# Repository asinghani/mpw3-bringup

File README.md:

# MPW3 Bringup / Characterization

Experiments in bringing up SKY130 MPW-3 chips from the initial tapeout in November 2021. Similarly to [MPW-1](https://github.com/asinghani/mpw1-bringup), the standardized "Caravel" padframe used in this tapeout had hold-time violations between 

## Breakout PCBs

- Characterization PCB [Schematic](boards/mpw3-common/schematic.pdf)
    - Independent voltage regulators for padframe and core (with non-volatile memory)
    - DS1077LU-50 clock generator with 50kHz - 50MHz output frequency + non-volatile memory
    - MCP23017 GPIO expanders for scanning chip I/Os
    - MCP1319 reset supervisor
    - MicroMod-style socket for Caravel chip breakout

- FTDI Breakout [Schematic](boards/uart-breakout/schematic.pdf)
    - Connects characterization PCB to FT232RL for UART access over USB
    - Includes LEDs, switches, and SPI FRAM for use with picoRF0 CPU

- VGA Breakout [Schematic](boards/vga-breakout/schematic.pdf)
    - Breaks out infinite-runner game and pong game to a 2-bit VGA DAC
    - Includes buffer chips for 

## Repo Structure

- `boards/` - KiCAD design files for breakout PCBs
- `parts/` - I/O characterization results for several dies
- `scripts/i2c_iface.py` - Script for interfacing with the voltage regulators, clock generator, and GPIO expanders on the characterization board
- `programs/` - Programs for running on the Caravel processor for the different applications
    - `aes_test.c` - Test the AES core on crypto-accelerator-chip-v2 design
    - `gpio_config_io_dino.py` - GPIO configuration for the VGA runner game
    - `gpio_config_io_pong.py` - GPIO configuration for the VGA pong game
    - `picorf0_test.c` - Test program for the picoRF0 custom CPU core
    - `read_ident.c` - Reads the ROM identifier and build number in the SHA and AES cores
    - `sha256_test.c` - Test the SHA256 core with some test vectors
    - `spi_fram.c` - Test program for using the Caravel SPI master to interface with an FRAM chip
    - `uart_working.c` - Workaround for UART RX on MPW-3 Caravel

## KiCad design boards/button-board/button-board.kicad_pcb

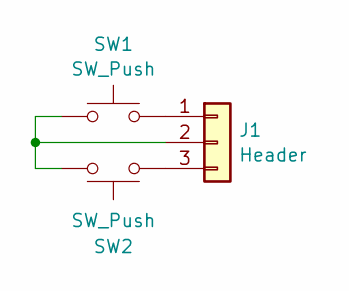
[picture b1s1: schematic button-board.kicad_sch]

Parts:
J1: Header; PinHeader_1x03_P2.54mm_Horizontal
SW1, SW2: SW_Push; SW_Cherry_MX_1.00u_PCB

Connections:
unnamed: J1.1, SW1.2
unnamed: J1.2, SW1.1, SW2.2
unnamed: J1.3, SW2.1

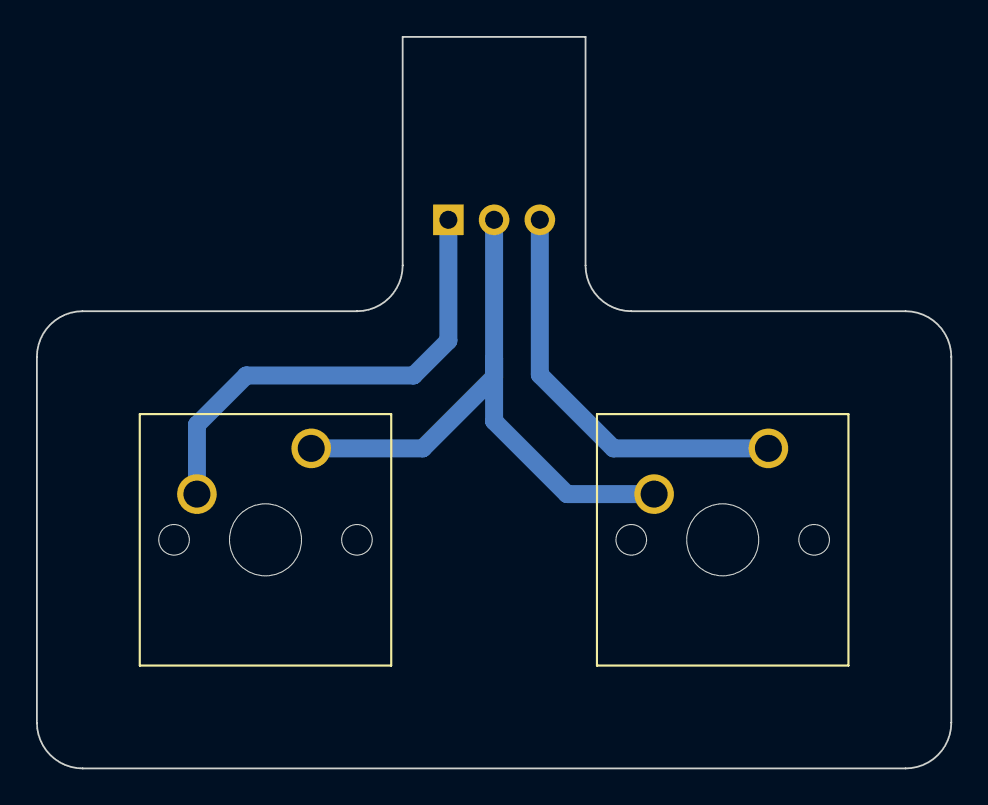
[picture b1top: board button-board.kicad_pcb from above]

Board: 2 copper layers, 50.8 x 40.6 mm, 3 parts (0 on the bottom side), 3 nets.

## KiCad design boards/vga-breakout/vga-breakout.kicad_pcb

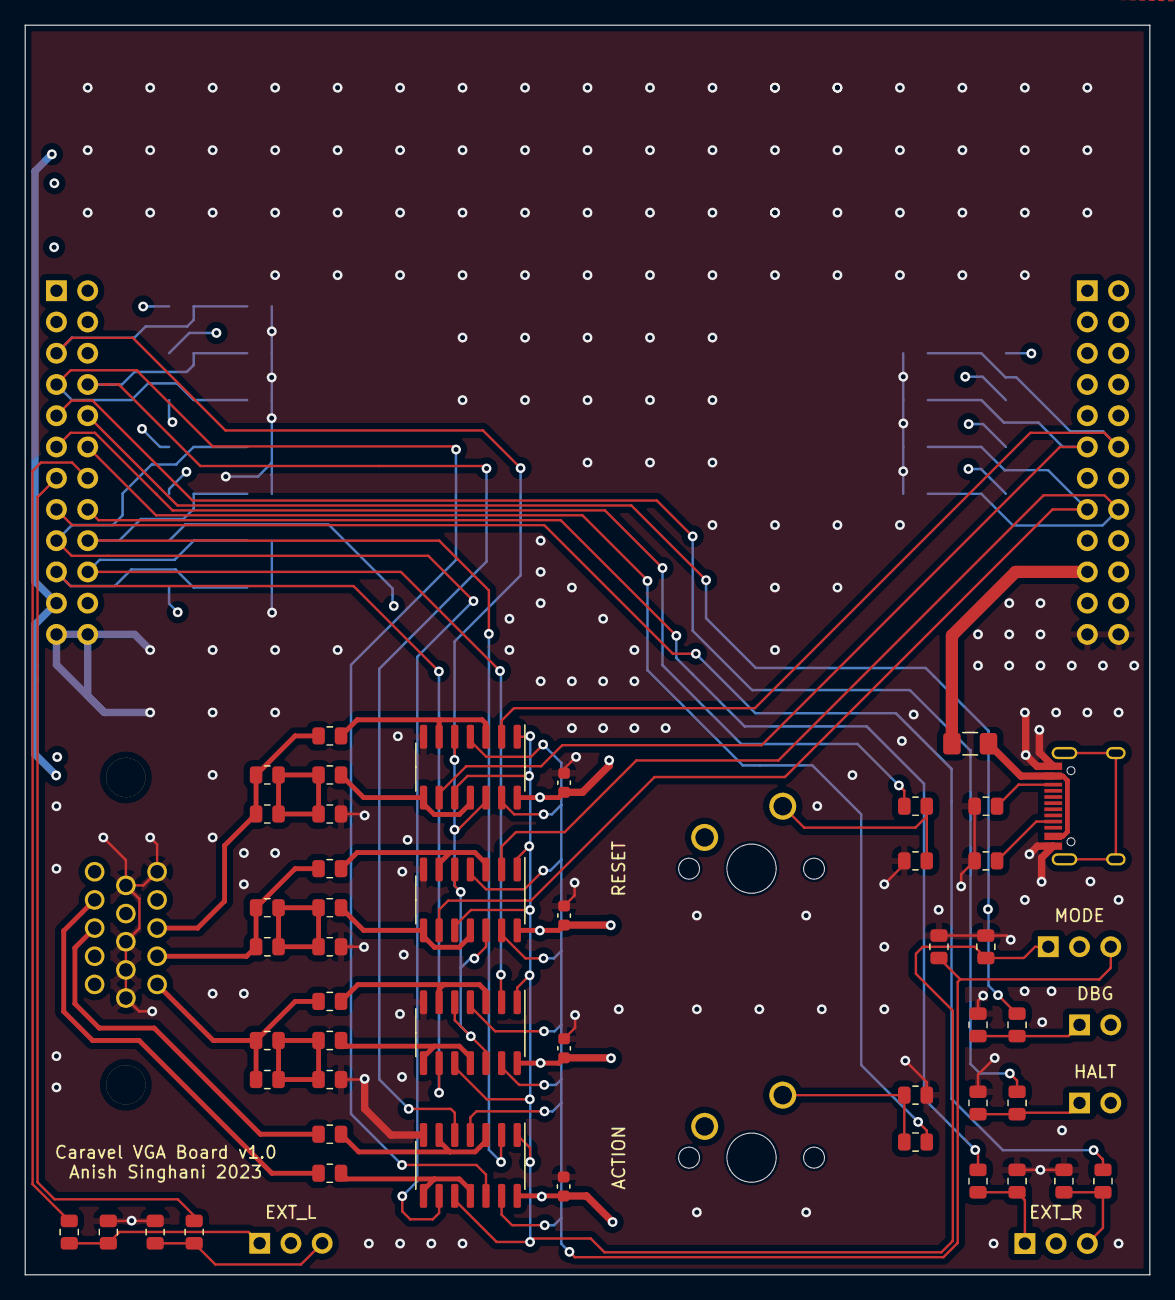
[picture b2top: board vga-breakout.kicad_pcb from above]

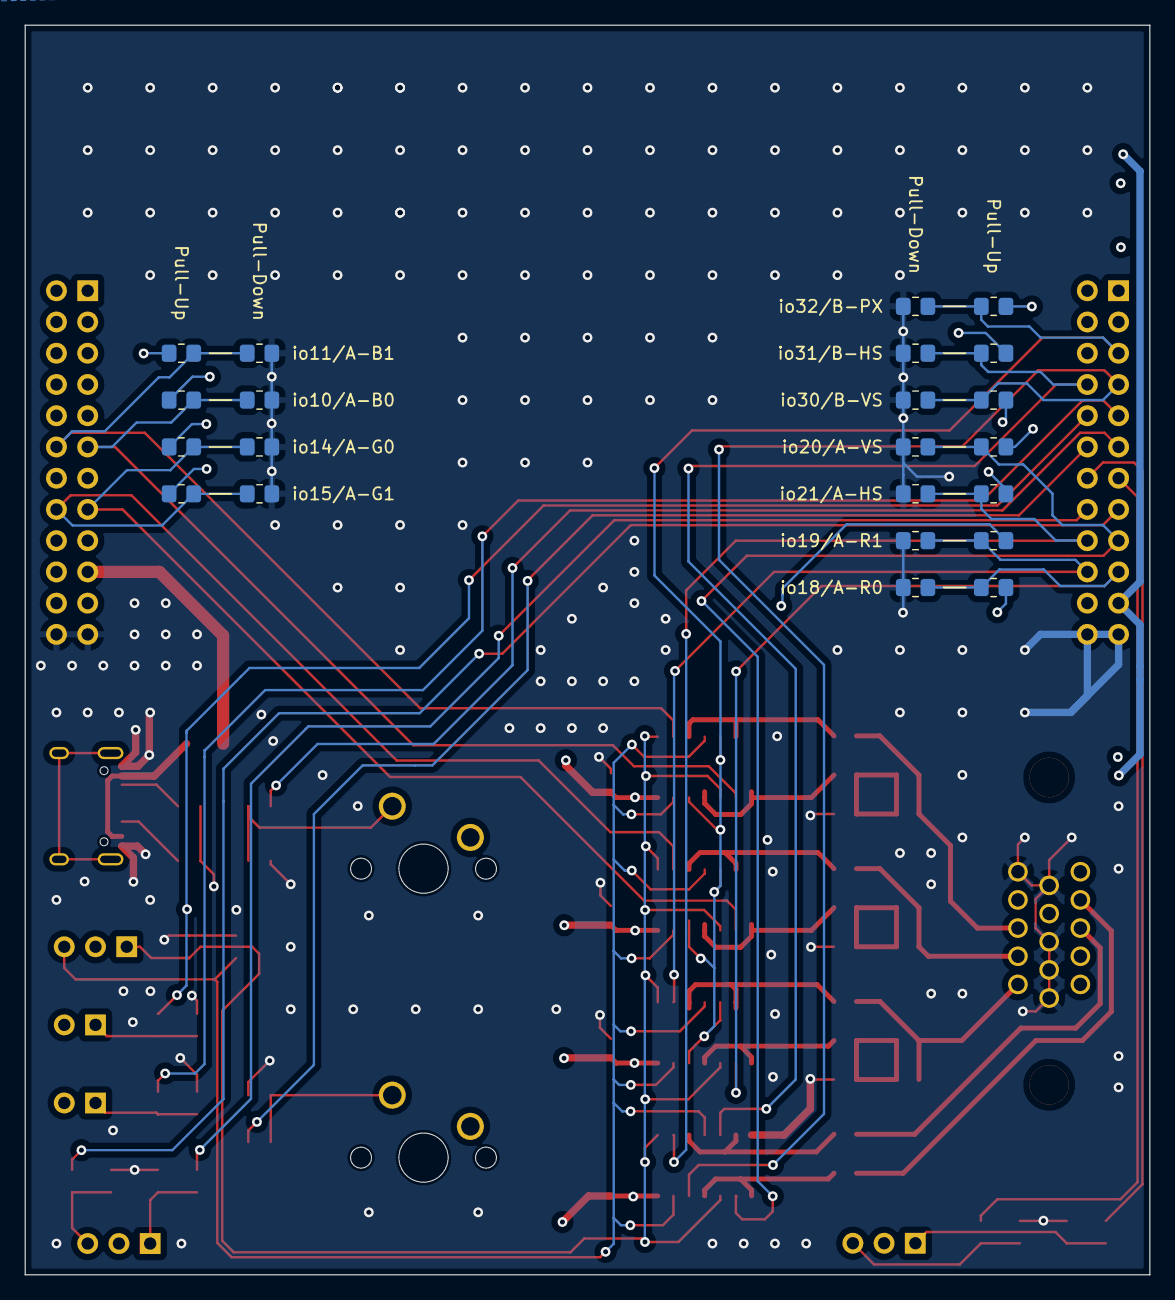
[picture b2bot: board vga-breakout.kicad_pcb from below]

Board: 4 copper layers, 91.4 x 101.6 mm, 79 parts (22 on the bottom side), 51 nets.

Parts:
C2, C3, C4, C5: 1u; C_0603_1608Metric
F1: 500mA; Fuse_1206_3216Metric_Pad1.42x1.75mm_HandSolder
J1: HDR_LEFT; PinHeader_2x12_P2.54mm_Vertical
J2: HDR_RIGHT; PinHeader_2x12_P2.54mm_Vertical
J3: USB_C_Receptacle_USB2.0; USB_C_Receptacle_HRO_TYPE-C-31-M-12
J4: VGA_PLUG; CONN_L77HDE15SD1CH4FVGA_AMP
J5: P1_HDR; PinSocket_1x03_P2.54mm_Vertical
J6: P2_HDR; PinSocket_1x03_P2.54mm_Vertical
JP1: DBG_JMP; PinSocket_1x02_P2.54mm_Vertical
JP2: HALT_JMP; PinSocket_1x02_P2.54mm_Vertical
JP3: MODE_JMP; PinSocket_1x03_P2.54mm_Vertical
R1, R2: 5.1K; R_0805_2012Metric
R3, R4, R5, R6, R11, R12, R13, R14, R66, R67: 10K; R_0805_2012Metric
R7, R8, R9, R10, R15, R16, R68, R69: 1K; R_0805_2012Metric
R17, R18, R19, R20, R21, R22, R23, R24, R25, R26, R29, R30, R31, R32, R37, R38, R39, R40, R45, R46, R47, R48: DNF; R_0805_2012Metric_Pad1.20x1.40mm_HandSolder
R49, R50: 100R; R_0805_2012Metric
R51, R52, R53, R54, R55, R56, R57, R58, R59, R60, R61, R62, R63, R64, R65: 330R; R_0805_2012Metric
SW1: BTN_ACT; SW_Cherry_MX_1.00u_PCB
SW2: BTN_RST; SW_Cherry_MX_1.00u_PCB
U2, U3, U4, U5: M74HC126; SO-14_3.9x8.65mm_P1.27mm

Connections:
+3V3: C2.1, C3.1, C4.1, C5.1, J1.21, J5.2, J6.2, JP1.2 (B), JP2.2 (B), JP3.2 (C), R17.2, R19.2, R21.2, R23.2, R25.2, R29.2, R31.2, R37.2, R39.2, R45.2, R47.2, SW1.2, SW2.2, U2.14 (VCC), U3.14 (VCC), U4.14 (VCC), U5.14 (VCC)
+5V: F1.1, J2.19
A_B: J4.3, R63.2, R64.2, R65.1
A_G: J4.2, R58.2, R59.2, R60.1
A_HS: J4.13, R49.2
A_R: J4.1, R51.2, R52.2, R55.1
A_VS: J4.14, R50.2
D_B0: R62.2, U5.8, U5.11
D_B1: R65.2, U5.3, U5.6
D_G0: R57.2, U4.8, U4.11
D_G1: R60.2, U4.3, U4.6
D_HS: R49.1, U2.3, U2.6
D_R0: R54.2, U3.8, U3.11
D_R1: R55.2, U3.3, U3.6
D_VS: R50.1, U2.8, U2.11
GND: C2.2, C3.2, C4.2, C5.2, J1.23, J1.24, J2.23, J2.24, J3.A1 (GND), J3.A12 (GND), J3.B1 (GND), J3.B12 (GND), J4.5, J4.6, J4.7, J4.8, J4.10, R1.1, R2.1, R3.1, R4.1, R5.1, R6.1, R11.1, R12.1, R13.1, R14.1, R18.1, R20.1, R22.1, R24.1, R26.1, R30.1, R32.1, R38.1, R40.1, R46.1, R48.1, R53.1, R56.1, R61.1, R66.1, R67.1, U2.7 (GND), U3.7 (GND), U4.7 (GND), U5.7 (GND)
MODE_A: JP3.1 (A), R67.2, U2.1, U2.10, U3.1, U3.10, U4.1, U4.10, U5.1, U5.10
MODE_B: JP3.3 (B), R66.2, U2.4, U2.13, U3.4, U3.13, U4.4, U4.13, U5.4, U5.13
unnamed: F1.2, J3.A4 (VBUS), J3.A9 (VBUS), J3.B4 (VBUS), J3.B9 (VBUS)
unnamed: J3.A5 (CC1), R1.2
unnamed: J3.B5 (CC2), R2.2
unnamed: J5.1, R9.2, R12.2
unnamed: J5.3, R10.2, R11.2
unnamed: J6.1, R13.2, R15.2
unnamed: J6.3, R14.2, R16.2
unnamed: JP1.1 (A), R3.2, R69.2
unnamed: JP2.1 (A), R4.2, R68.2
unnamed: R5.2, R7.2, SW2.1
unnamed: R6.2, R8.2, SW1.1
unnamed: R51.1, R52.1, R53.2, R54.1
unnamed: R56.2, R57.1, R58.1, R59.1
unnamed: R61.2, R62.1, R63.1, R64.1
mprj_io[10]: J2.11, R47.1, R48.2, U5.9
mprj_io[11]: J2.12, R45.1, R46.2, U5.2
mprj_io[14]: J2.15, R39.1, R40.2, U4.9
mprj_io[15]: J2.16, R37.1, R38.2, U4.2
mprj_io[18]: J1.19, R31.1, R32.2, U3.9
mprj_io[19]: J1.20, R29.1, R30.2, U3.2
mprj_io[20]: J1.17, R23.1, R24.2, U2.9
mprj_io[21]: J1.18, R21.1, R22.2, U2.2
mprj_io[22]: J1.15, R16.1
mprj_io[23]: J1.16, R15.1
mprj_io[24]: J1.13, R10.1
mprj_io[25]: J1.14, R9.1
mprj_io[26]: J1.11, R7.1
mprj_io[27]: J1.12, R8.1
mprj_io[28]: J1.9, R68.1
mprj_io[29]: J1.10, R69.1
mprj_io[30]: J1.7, R19.1, R20.2, U2.12
mprj_io[31]: J1.8, R17.1, R18.2, U2.5
mprj_io[32]: J1.5, R25.1, R26.2, U3.5, U3.12, U4.5, U4.12, U5.5, U5.12

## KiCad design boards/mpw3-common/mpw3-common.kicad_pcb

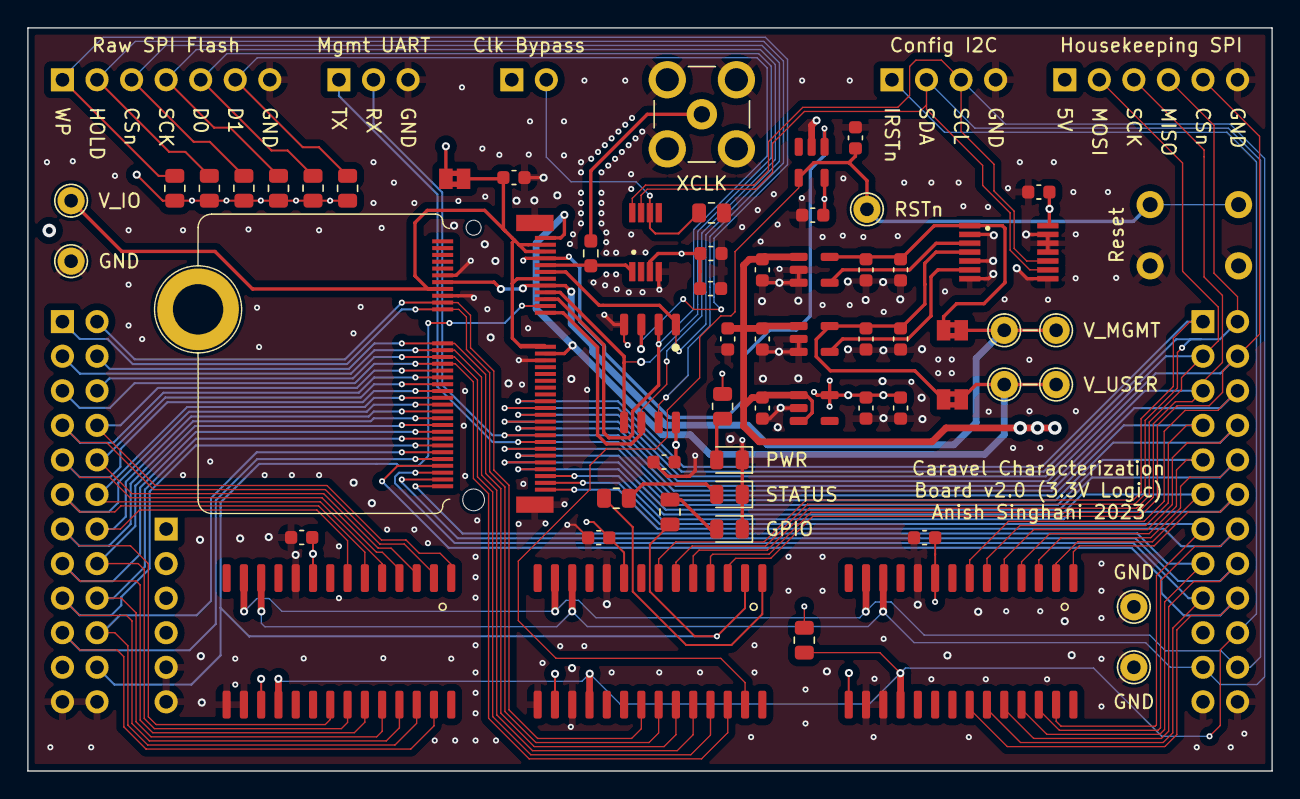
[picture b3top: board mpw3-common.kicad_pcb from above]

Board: 4 copper layers, 91.4 x 54.6 mm, 69 parts (0 on the bottom side), 67 nets.

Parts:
C1, C2, C7, C23, C24, C25, C26, C27: 0.1u; C_0603_1608Metric
C3, C5, C12, C13: 10u; C_0603_1608Metric
C4, C6, C10, C11, C14, C15, C16, C22: 1u; C_0603_1608Metric
D1: GPIO; LED_0805_2012Metric
D2: PWR; LED_0805_2012Metric
D3: DBG; LED_0805_2012Metric
H1: MICROMOD-Standoff; MicroMod-Standoff
J2: UART_HEADER; PinHeader_1x03_P2.54mm_Vertical
J3: FLASH_HEADER; PinHeader_1x07_P2.54mm_Vertical
J4: HKSPI_HEADER; PinHeader_1x06_P2.54mm_Vertical
J5: Conn_01x04; PinHeader_1x04_P2.54mm_Vertical
J7: PWR_OUT_HDR; PinHeader_1x06_P2.54mm_Vertical
J8: XCLK; SMB_Jack_Vertical
J9: HDR_LEFT; PinHeader_2x12_P2.54mm_Vertical
J10: HDR_RIGHT; PinHeader_2x12_P2.54mm_Vertical
JP2: JP_IO; SolderJumper-2_P1.3mm_Bridged2Bar_Pad1.0x1.5mm
JP3: JP_USER; SolderJumper-2_P1.3mm_Bridged2Bar_Pad1.0x1.5mm
JP4: JP_CARAVEL; SolderJumper-2_P1.3mm_Bridged2Bar_Pad1.0x1.5mm
JP5: CLK_DIS; PinHeader_1x02_P2.54mm_Vertical
R1, R2, R3, R4, R5, R6, R11, R13: 10K; R_0805_2012Metric
R7, R8, R9: 1K; R_0805_2012Metric
R10: 0R, DNF; R_0603_1608Metric_Pad0.98x0.95mm_HandSolder
SW1: BTN_RST; SW_PUSH_6mm
TP1: RST_TP; TestPoint_THTPad_D2.0mm_Drill1.0mm
TP4: 3V3_TP; TestPoint_THTPad_D2.0mm_Drill1.0mm
TP6, TP7: VU_TP; TestPoint_THTPad_D2.0mm_Drill1.0mm
TP8, TP9: VC_TP; TestPoint_THTPad_D2.0mm_Drill1.0mm
TP10, TP11, TP12: GND_TP; TestPoint_THTPad_D2.0mm_Drill1.0mm
U1: caravel-M.2-card; M.2-CONNECTOR-E
U2: MCP1319MT-29LE; SOT-23-5
U3: W25Q32JVSS; SOIC-8_5.23x5.23mm_P1.27mm
U4: MIC5504-3.3YM5; SOT-23-5
U5, U6: TPS76201; SOT-23-5
U7: TPL0102-100PWR; SOP65P640X120-14N
U8: DS1077LU-50; SOP65P490X110-8N
U9, U10, U11: MCP23017; SOIC-28W_7.5x17.9mm_P1.27mm

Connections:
+3V3: C1.1, C2.1, C5.2, C6.2, C22.1, C23.1, C24.1, C25.1, C26.1, C27.1, J7.3, J7.4, J9.21, JP2.1 (A), JP5.1 (A), R1.1, R2.1, R3.1, R4.1, R5.1, R6.1, R8.1, R11.1, U2.5 (VDD), U3.8 (VCC), U4.5 (VOUT), U7.14 (VDD), U8.3 (VCC), U9.9 (VDD), U9.15 (A0), U10.9 (VDD), U10.16 (A1), U11.9 (VDD), U11.17 (A2)
+5V: C3.2, C4.2, C10.2, C11.2, J4.1, J7.1, J7.2, J10.19, U4.1 (VIN), U4.3 (EN), U5.1 (IN), U6.1 (IN)
Caravel_CSB: J3.3, R6.2, U1.11 (Caravel_CSB), U3.1 (~CS)
Caravel_D0: J3.5, R4.2, U1.17 (Caravel_D0), U3.5 (DI(IO0))
Caravel_D1: J3.6, R3.2, U1.19 (Caravel_D1), U3.2 (DO(IO1))
Caravel_SCK: J3.4, R5.2, U1.23 (Caravel_SCK), U3.6 (CLK)
Flash_HOLD: J3.2, R1.2, U3.7 (IO3)
Flash_WP: J3.1, R2.2, U3.3 (IO2)
GND: C1.2, C2.2, C3.1, C4.1, C5.1, C6.1, C7.2, C10.1, C11.1, C12.1, C13.1, C14.1, C15.1, C16.2, C22.2, C23.2, C24.2, C25.2, C26.2, C27.2, D1.1 (K), D2.1 (K), D3.1 (K), J2.3, J3.7, J4.6, J5.4, J7.5, J7.6, J8.2 (Ext), J9.23, J9.24, J10.23, J10.24, R13.2, SW1.2, TP10.1, TP11.1, TP12.1, U1.12 (GND), U1.18 (GND), U1.37 (GND), U1.A1 (GND), U1.A2 (GND), U2.2 (VSS), U3.4 (GND), U4.2 (GND), U5.2 (GND), U5.3 (~EN), U6.2 (GND), U6.3 (~EN), U7.2 (LA), U7.5 (LB), U7.7 (A2), U7.8 (VSS), U7.11 (GND), U7.12 (A1), U7.13 (AO), U8.4 (GND), U9.10 (VSS), U9.16 (A1), U9.17 (A2), U10.10 (VSS), U10.15 (A0), U10.17 (A2), U11.10 (VSS), U11.15 (A0), U11.16 (A1)
I2C_RSTn: J5.1, J10.20, R11.2, U9.18 (~RESET), U10.18 (~RESET), U11.18 (~RESET)
I2C_SCL: J5.3, J10.21, U7.10 (SCL), U8.8 (SCL), U9.12 (SCK), U10.12 (SCK), U11.12 (SCK)
I2C_SDA: J5.2, J10.22, U7.9 (SDA), U8.7 (SDA), U9.13 (SDA), U10.13 (SDA), U11.13 (SDA)
unnamed: D1.2 (A), R7.2
unnamed: D2.2 (A), R8.2
unnamed: D3.2 (A), R9.2
unnamed: J8.1 (In), R10.1
unnamed: JP5.2 (B), R13.1, U8.6 (CTRL1)
REG1_FB: U5.4 (FB), U7.3 (WA)
REG1_OUT: C12.2, C14.2, JP4.1 (A), U5.5 (OUT), U7.1 (HA)
REG2_FB: U6.4 (FB), U7.6 (WB)
REG2_OUT: C13.2, C15.2, JP3.1 (A), U6.5 (OUT), U7.4 (HB)
dbg_led: R9.1, U10.1 (GPB0)
gpio: J9.22, R7.1, U1.21 (gpio), U10.2 (GPB1)
mprj_io[0]: J10.1, U1.49 (mprj_io[0]), U10.7 (GPB6)
mprj_io[1]_SDO: J4.4, J10.2, U1.51 (mprj_io[1]_SDO), U10.6 (GPB5)
mprj_io[2]_SDI: J4.2, J10.3, U1.53 (mprj_io[2]_SDI), U10.5 (GPB4)
mprj_io[3]_CSB: J4.5, J10.4, U1.55 (mprj_io[3]_CSB), U10.3 (GPB2)
mprj_io[4]_SCK: J4.3, J10.5, U1.57 (mprj_io[4]_SCK), U10.4 (GPB3)
mprj_io[5]_ser_rx: J2.2, J10.6, U1.59 (mprj_io[5]_ser_rx), U9.7 (GPB6)
mprj_io[6]_ser_tx: J2.1, J10.7, U1.61 (mprj_io[6]_ser_tx), U9.6 (GPB5)
mprj_io[7]: J10.8, U1.63 (mprj_io[7]), U9.5 (GPB4)
mprj_io[8]: J10.9, U1.65 (mprj_io[8]), U9.4 (GPB3)
mprj_io[9]: J10.10, U1.67 (mprj_io[9]), U9.3 (GPB2)
mprj_io[10]: J10.11, U1.69 (mprj_io[10]), U9.2 (GPB1)
mprj_io[11]: J10.12, U1.71 (mprj_io[11]), U9.1 (GPB0)
mprj_io[12]: J10.13, U1.73 (mprj_io[12]), U9.27 (GPA6)
mprj_io[13]: J10.14, U1.75 (mprj_io[13]), U9.26 (GPA5)
mprj_io[14]: J10.15, U1.74 (mprj_io[14]), U9.25 (GPA4)
mprj_io[15]: J10.16, U1.72 (mprj_io[15]), U9.24 (GPA3)
mprj_io[16]: J10.17, U1.70 (mprj_io[16]), U9.23 (GPA2)
mprj_io[17]: J10.18, U1.68 (mprj_io[17]), U9.22 (GPA1)
mprj_io[18]: J9.19, U1.66 (mprj_io[18]), U11.27 (GPA6)
mprj_io[19]: J9.20, U1.64 (mprj_io[19]), U11.26 (GPA5)
mprj_io[20]: J9.17, U1.62 (mprj_io[20]), U11.25 (GPA4)
mprj_io[21]: J9.18, U1.60 (mprj_io[21]), U11.24 (GPA3)
mprj_io[22]: J9.15, U1.58 (mprj_io[22]), U11.23 (GPA2)
mprj_io[23]: J9.16, U1.56 (mprj_io[23]), U11.22 (GPA1)
mprj_io[24]: J9.13, U1.54 (mprj_io[24]), U11.21 (GPA0)
mprj_io[25]: J9.14, U1.52 (mprj_io[25]), U11.7 (GPB6)
mprj_io[26]: J9.11, U1.50 (mprj_io[26]), U11.6 (GPB5)
mprj_io[27]: J9.12, U1.48 (mprj_io[27]), U11.5 (GPB4)
mprj_io[28]: J9.9, U1.46 (mprj_io[28]), U11.4 (GPB3)
mprj_io[29]: J9.10, U1.44 (mprj_io[29]), U11.3 (GPB2)
mprj_io[30]: J9.7, U1.42 (mprj_io[30]), U11.2 (GPB1)
mprj_io[31]: J9.8, U1.40 (mprj_io[31]), U11.1 (GPB0)
mprj_io[32]: J9.5, U1.38 (mprj_io[32]), U10.26 (GPA5)
mprj_io[33]: J9.6, U1.36 (mprj_io[33]), U10.25 (GPA4)
mprj_io[34]: J9.3, U1.34 (mprj_io[34]), U10.24 (GPA3)
mprj_io[35]: J9.4, U1.32 (mprj_io[35]), U10.23 (GPA2)
mprj_io[36]: J9.1, U1.22 (mprj_io[36]), U10.22 (GPA1)
mprj_io[37]: J9.2, U1.20 (mprj_io[37]), U10.21 (GPA0)
vccd: JP4.2 (B), TP8.1, TP9.1, U1.14 (vccd), U1.15 (vcdd)
vccd1: JP3.2 (B), TP6.1, TP7.1, U1.1 (vccd2), U1.35 (vccd1)
vdda: C16.1, JP2.2 (B), TP4.1, U1.3 (vddio), U1.5 (vdda), U1.13 (vdda2), U1.16 (vddio), U1.33 (vdda1)
xclk: R10.2, U1.9 (xclk), U8.1 (OUT1)
~MR: C7.1, SW1.1, TP1.1, U2.4 (~MR), U10.27 (GPA6)
~RST: U1.7 (~RST), U2.1 (~RST)

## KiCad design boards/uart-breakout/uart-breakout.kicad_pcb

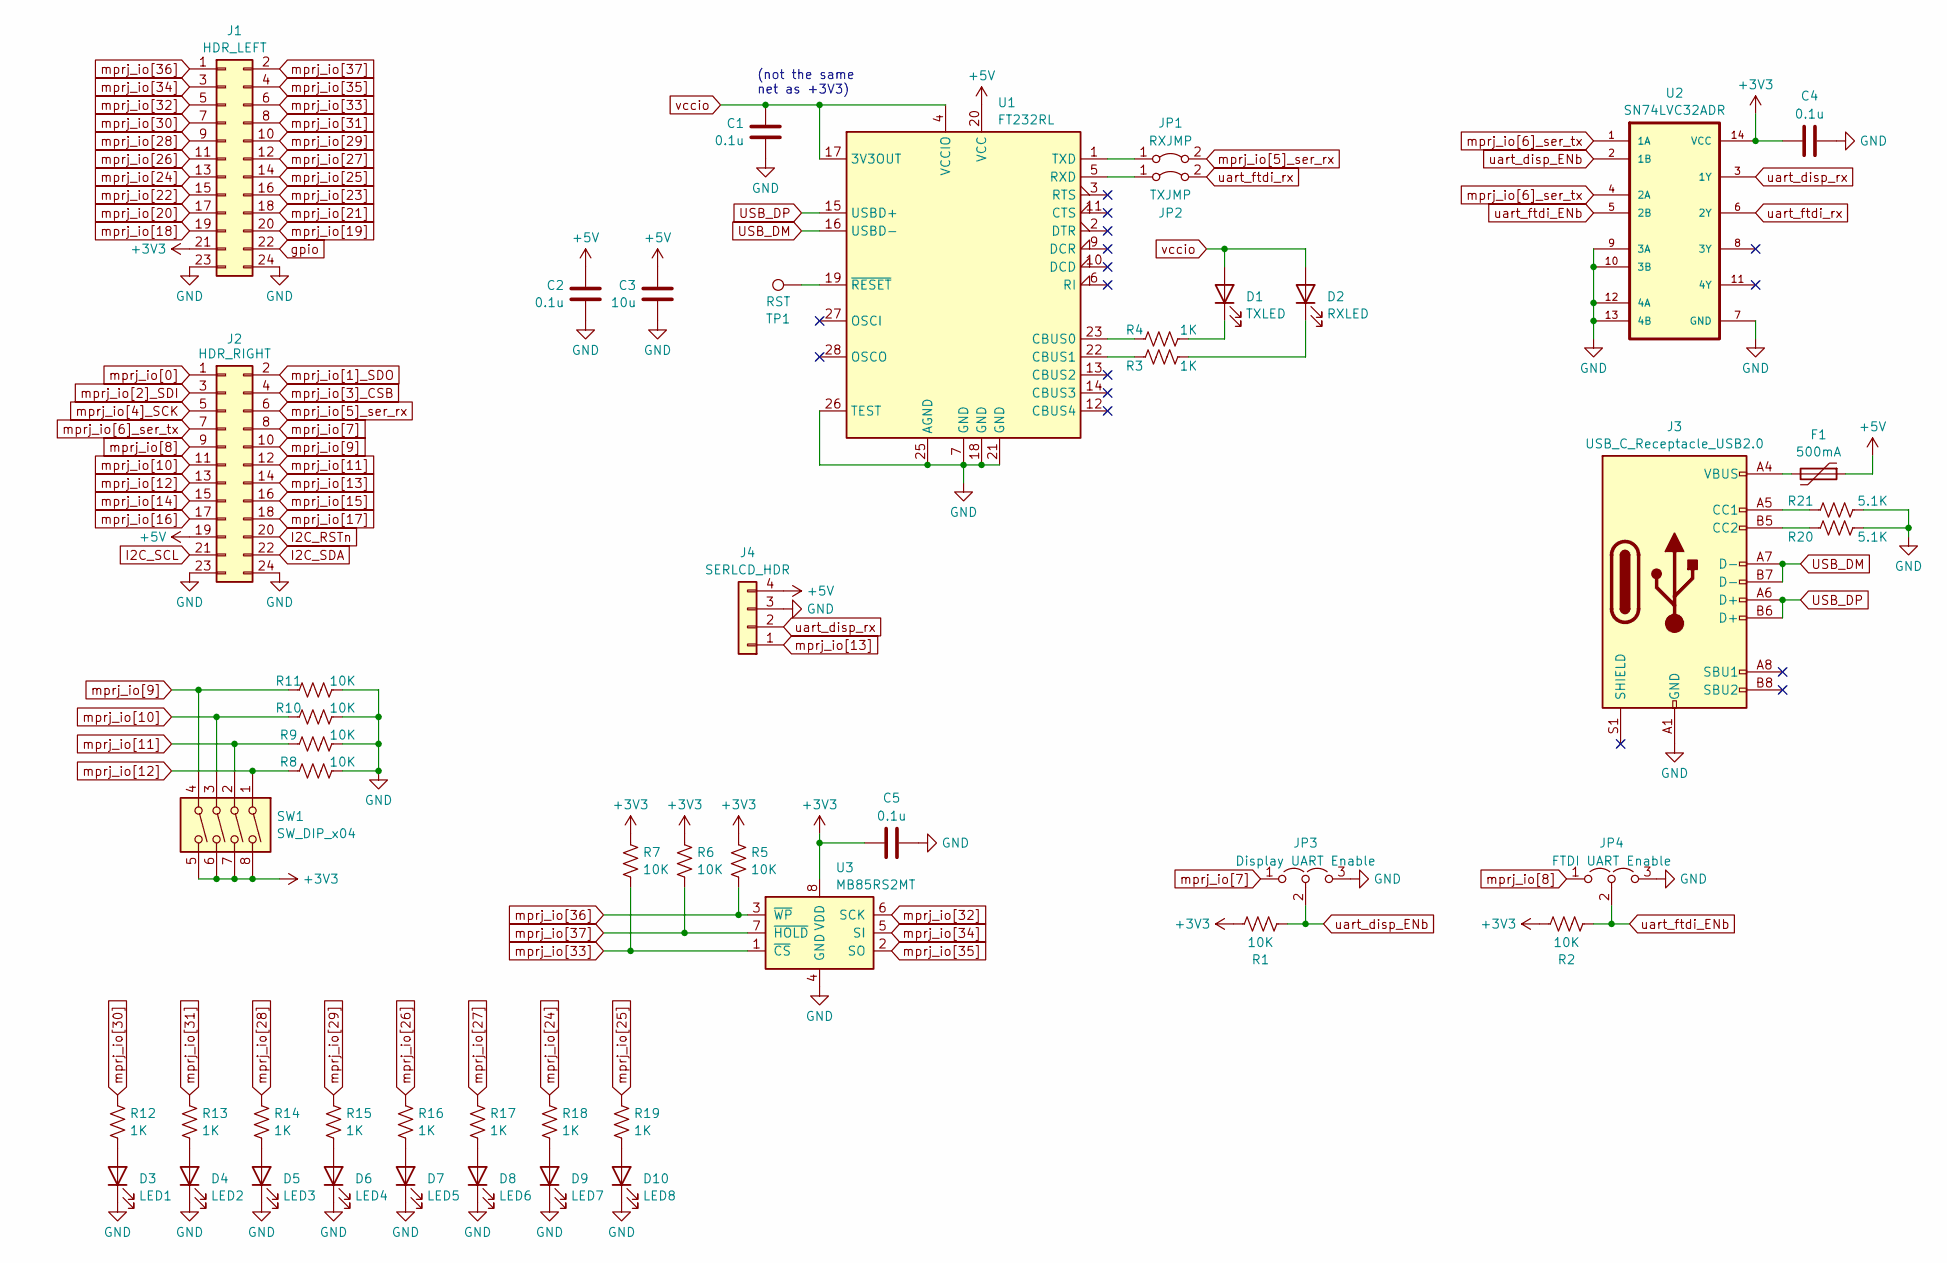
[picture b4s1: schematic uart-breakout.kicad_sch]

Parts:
C1, C2, C4, C5: 0.1u; C_0603_1608Metric; LCSC C14663
C3: 10u; C_0603_1608Metric; LCSC C19702
D1: TXLED; LED_0805_2012Metric; LCSC C284931
D2: RXLED; LED_0805_2012Metric; LCSC C284931
D3: LED1; LED_0805_2012Metric; LCSC C98221
D4: LED2; LED_0805_2012Metric; LCSC C98221
D5: LED3; LED_0805_2012Metric; LCSC C98221
D6: LED4; LED_0805_2012Metric; LCSC C98221
D7: LED5; LED_0805_2012Metric; LCSC C98221
D8: LED6; LED_0805_2012Metric; LCSC C98221
D9: LED7; LED_0805_2012Metric; LCSC C98221
D10: LED8; LED_0805_2012Metric; LCSC C98221
F1: 500mA; Fuse_1206_3216Metric_Pad1.42x1.75mm_HandSolder; LCSC C720075
J1: HDR_LEFT; PinHeader_2x12_P2.54mm_Vertical
J2: HDR_RIGHT; PinHeader_2x12_P2.54mm_Vertical
J3: USB_C_Receptacle_USB2.0; USB_C_Receptacle_HRO_TYPE-C-31-M-12; LCSC C5185005
J4: SERLCD_HDR; PinHeader_1x04_P2.54mm_Vertical
JP1: RXJMP; SolderJumper-2_P1.3mm_Bridged_Pad1.0x1.5mm
JP2: TXJMP; SolderJumper-2_P1.3mm_Bridged_Pad1.0x1.5mm
JP3: Display UART Enable; PinHeader_1x03_P2.54mm_Vertical
JP4: FTDI UART Enable; PinHeader_1x03_P2.54mm_Vertical
R1, R2, R5, R6, R7, R8, R9, R10, R11: 10K; R_0805_2012Metric; LCSC C17414
R3, R4, R12, R13, R14, R15, R16, R17, R18, R19: 1K; R_0805_2012Metric_Pad1.20x1.40mm_HandSolder; LCSC C17513
R20, R21: 5.1K; R_0805_2012Metric; LCSC C27834
SW1: SW_DIP_x04; SW_DIP_SPSTx04_Slide_6.7x11.72mm_W7.62mm_P2.54mm_LowProfile
TP1: RST; TestPoint_Pad_D1.5mm
U1: FT232RL; SSOP-28_5.3x10.2mm_P0.65mm; LCSC C8690
U2: SN74LVC32ADR; SOIC127P600X175-14N; LCSC C7852
U3: MB85RS2MT; SOIC-8_3.9x4.9mm_P1.27mm; LCSC C189908

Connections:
+3V3: C4.2, C5.2, J1.21, R1.2, R2.2, R5.1, R6.1, R7.1, SW1.5, SW1.6, SW1.7, SW1.8, U2.14 (VCC), U3.8 (VDD)
+5V: C2.1, C3.1, F1.1, J2.19, J4.4, U1.20 (VCC)
GND: C1.2, C2.2, C3.2, C4.1, C5.1, D3.1 (K), D4.1 (K), D5.1 (K), D6.1 (K), D7.1 (K), D8.1 (K), D9.1 (K), D10.1 (K), J1.23, J1.24, J2.23, J2.24, J3.A1 (GND), J3.A12 (GND), J3.B1 (GND), J3.B12 (GND), J4.3, JP3.3 (B), JP4.3 (B), R8.2, R9.2, R10.2, R11.2, R20.1, R21.1, U1.7 (GND), U1.18 (GND), U1.21 (GND), U1.25 (AGND), U1.26 (TEST), U2.7 (GND), U2.9 (3A), U2.10 (3B), U2.12 (4A), U2.13 (4B), U3.4 (GND)
I2C_RSTn: J2.20
I2C_SCL: J2.21
I2C_SDA: J2.22
unnamed: D1.1 (K), R4.2
unnamed: D2.1 (K), R3.1
unnamed: D3.2 (A), R12.2
unnamed: D4.2 (A), R13.2
unnamed: D5.2 (A), R14.2
unnamed: D6.2 (A), R15.2
unnamed: D7.2 (A), R16.2
unnamed: D8.2 (A), R17.2
unnamed: D9.2 (A), R18.2
unnamed: D10.2 (A), R19.2
unnamed: F1.2, J3.A4 (VBUS), J3.A9 (VBUS), J3.B4 (VBUS), J3.B9 (VBUS)
unnamed: J3.A5 (CC1), R21.2
unnamed: J3.B5 (CC2), R20.2
unnamed: JP1.1 (A), U1.1 (TXD)
unnamed: JP2.1 (A), U1.5 (RXD)
unnamed: R4.1, U1.23 (CBUS0)
unnamed: R3.2, U1.22 (CBUS1)
unnamed: TP1.1, U1.19 (~RESET)
USB_DM: J3.A7 (D-), J3.B7 (D-), U1.16 (USBD-)
USB_DP: J3.A6 (D+), J3.B6 (D+), U1.15 (USBD+)
gpio: J1.22
mprj_io[0]: J2.1
mprj_io[1]_SDO: J2.2
mprj_io[2]_SDI: J2.3
mprj_io[3]_CSB: J2.4
mprj_io[4]_SCK: J2.5
mprj_io[5]_ser_rx: J2.6, JP1.2 (B)
mprj_io[6]_ser_tx: J2.7, U2.1 (1A), U2.4 (2A)
mprj_io[7]: J2.8, JP3.1 (A)
mprj_io[8]: J2.9, JP4.1 (A)
mprj_io[9]: J2.10, R11.1, SW1.4
mprj_io[10]: J2.11, R10.1, SW1.3
mprj_io[11]: J2.12, R9.1, SW1.2
mprj_io[12]: J2.13, R8.1, SW1.1
mprj_io[13]: J2.14, J4.1
mprj_io[14]: J2.15
mprj_io[15]: J2.16
mprj_io[16]: J2.17
mprj_io[17]: J2.18
mprj_io[18]: J1.19
mprj_io[19]: J1.20
mprj_io[20]: J1.17
mprj_io[21]: J1.18
mprj_io[22]: J1.15
mprj_io[23]: J1.16
mprj_io[24]: J1.13, R18.1
mprj_io[25]: J1.14, R19.1
mprj_io[26]: J1.11, R16.1
mprj_io[27]: J1.12, R17.1
mprj_io[28]: J1.9, R14.1
mprj_io[29]: J1.10, R15.1
mprj_io[30]: J1.7, R12.1
mprj_io[31]: J1.8, R13.1
mprj_io[32]: J1.5, U3.6 (SCK)
mprj_io[33]: J1.6, R7.2, U3.1 (~CS)
mprj_io[34]: J1.3, U3.5 (SI)
mprj_io[35]: J1.4, U3.2 (SO)
mprj_io[36]: J1.1, R5.2, U3.3 (~WP)
mprj_io[37]: J1.2, R6.2, U3.7 (~HOLD)
uart_disp_ENb: JP3.2 (C), R1.1, U2.2 (1B)
uart_disp_rx: J4.2, U2.3 (1Y)
uart_ftdi_ENb: JP4.2 (C), R2.1, U2.5 (2B)
uart_ftdi_rx: JP2.2 (B), U2.6 (2Y)
vccio: C1.1, D1.2 (A), D2.2 (A), U1.4 (VCCIO), U1.17 (3V3OUT)

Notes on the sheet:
(not the same net as +3V3)

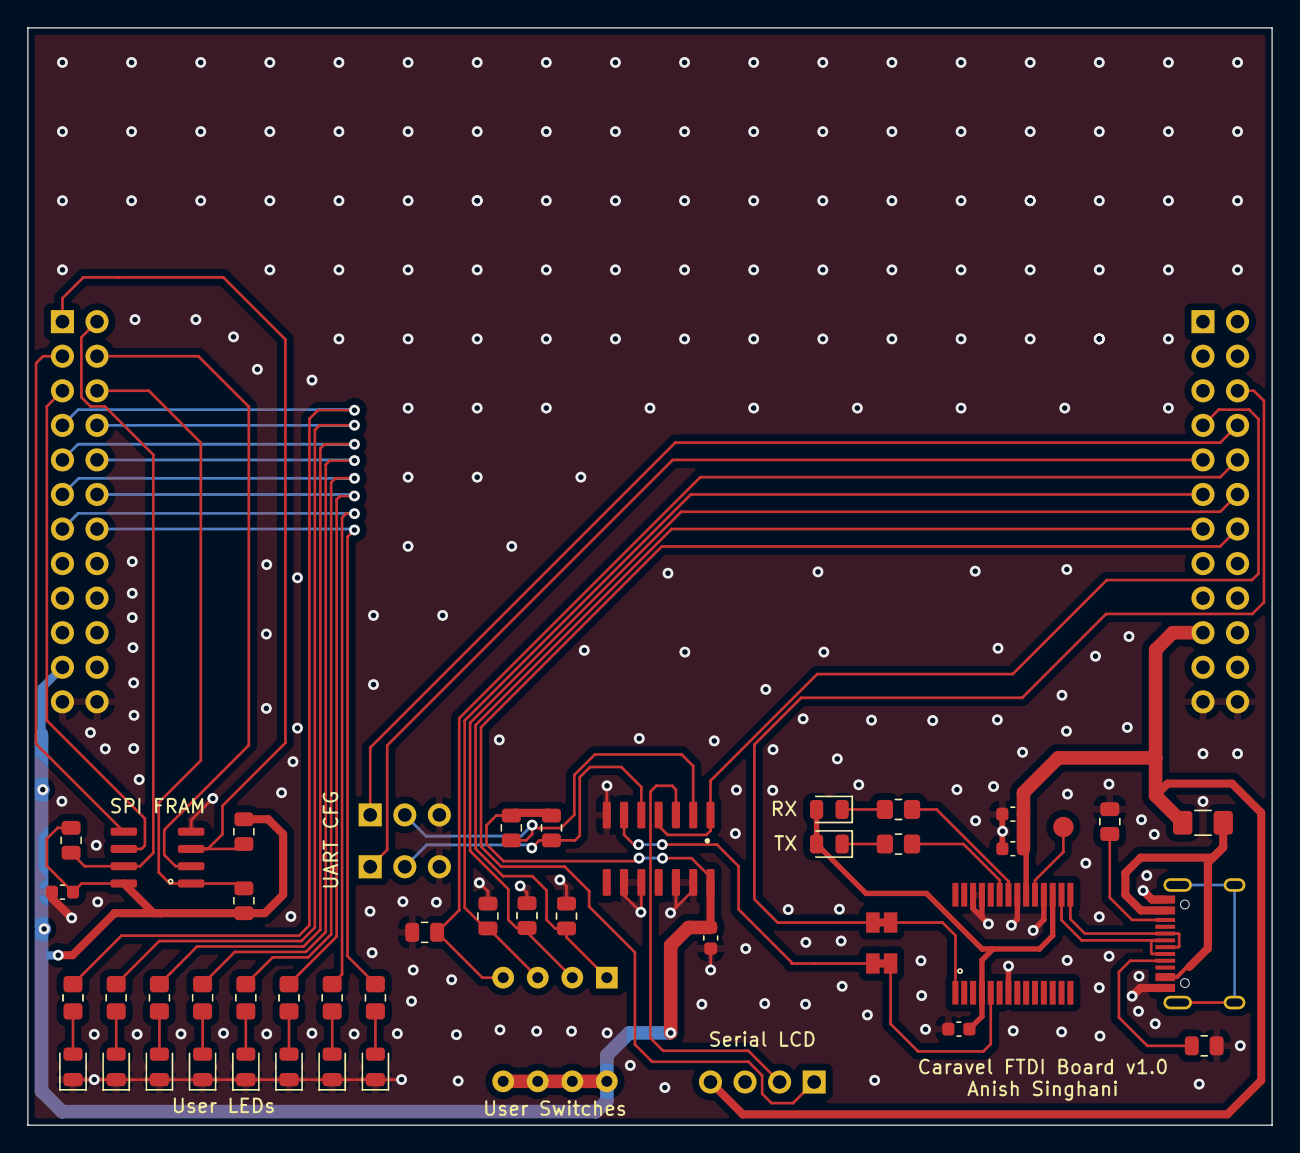
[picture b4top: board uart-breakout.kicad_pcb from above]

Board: 2 copper layers, 91.4 x 80.6 mm, 50 parts (0 on the bottom side), 51 nets.

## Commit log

2023-12-14 initial checkin
2023-12-14 import programs
